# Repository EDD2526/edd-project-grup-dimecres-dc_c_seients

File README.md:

View this project on [CADLAB.io](https://cadlab.io/project/30193). 

# Projecte Seients

>**Autors: MIGUEL Angel Tovar Jaime - Pol Salas Costa** 
>**Versió: 3.8**

----------

## Objectiu

>Dissenyar una Unitat de Control Electrònic (ECU) per al control dels seients, capaç de gestionar la posició, memòria de la posició i l'escalfador del seient, comunicant-se amb la resta del vehicle mitjançant bus CAN.

## Diagrama de blocs

### Descripció/funcionalitat de cada bloc

  * **Processament Lògic:** Microcontrolador PIC24HJ128GP502 a 3.3V encarregat de l'execució del firmware i gestió de perifèrics
  * **Alimentació:** Sistema de doble regulació. Un convertidor LM2596 que redueix els 12V de la bateria a 5V per a comunicacions, i un regulador LM1117 que  proporciona 3.3V nets per a la lògica digital
  * **Control de Potència:** Controlador PWM actuant a través del bus I2C, PCA9685, per accionar els drivers dels 3 motors (posició, altura, reclinació). S'inclou un MOSFET per al control de la manta calefactora
  * **Emmagatzematge:** Memòria EEPROM I2C, 24LC256, per desar de forma no volàtil certes posicions dels seients
  * **Interfícies de Comunicació:** Transceptor MCP2562-E-SN per a connexió al bus CAN del vehicle, i MAX3232 per adaptar els nivells lògics UART a RS232 per a depuració mitjançant connector DE-9
  * **Entrades/Sensors:** Connectors per a la botonera d'usuari i finals de cursa

-----------

## Requisits / Especificacions

  * Alimentació d'entrada: 12V DC
  * Tensions de regulació interna: 5V DC i 3.3V DC
  * Microcontrolador: PIC24HJ128GP502
  * Freqüència de rellotge: Cristall extern de 8 MHz
  * Entrades digitals: 6 botons de control de seient i 3 finals de cursa agrupats
  * Comunicacions: Bus CAN, bus I2C, i port sèrie UART/RS232

-----------

## Components

| Descripció | Ref | Package | Datasheet | Proveïdor | Preu | Unitats |
| --- | --- | --- | --- | --- | --- | --- |
| Microcontrolador | PIC24HJ128GP502 | SOIC-28 | [Datasheet](https://www.microchip.com/en-us/product/PIC24HJ128GP502) | Mouser | 4,50&euro; | 1x |
| Controlador PWM I2C | PCA9685BS | HVQFN-28 | [Datasheet](https://www.nxp.com/docs/en/data-sheet/PCA9685.pdf) | Mouser | 2,10&euro; | 1x |
| Driver de Motor (Pont H) | DRV8871 | HSOP-8 | [Datasheet](https://www.ti.com/lit/ds/symlink/drv8871.pdf) | Mouser | 1,50&euro; | 3x |
| MOSFET de potència | IRLZ44N | TO-220 | [Datasheet](https://www.infineon.com/dgdl/irlz44n.pdf?fileId=5546d462533600a40153567206892720) | Mouser | 0,90&euro; | 1x |
| Memòria EEPROM I2C | 24LC256 | SOIC-8 | [Datasheet](https://ww1.microchip.com/downloads/en/DeviceDoc/21203M.pdf) | Mouser | 0,60&euro; | 1x |
| Transceptor CAN | MCP2562-E-SN | SOIC-8 | [Datasheet](https://ww1.microchip.com/downloads/en/DeviceDoc/20005167C.pdf) | Mouser | 1,10&euro; | 1x |
| Transceptor RS232 | MAX3232 | SOIC-16 | [Datasheet](https://www.ti.com/lit/ds/symlink/max3232.pdf) | Mouser | 1,20&euro; | 1x |
| Expansor I/O I2C | PCF8574T | SOIC-16 | [Datasheet](https://www.ti.com/lit/ds/symlink/pcf8574.pdf) | Mouser | 1,30&euro; | 1x |
| Regulador (12V a 5V) | LM2596 | TO-263 | [Datasheet](https://www.ti.com/lit/ds/symlink/lm2596.pdf) | Mouser | 1,50&euro; | 1x |
| Regulador (5V a 3.3V) | LM1117 | TO-252 | [Datasheet](https://www.ti.com/lit/ds/symlink/lm1117.pdf) | Mouser | 0,80&euro; | 1x |
| Connector RS232 | DE-9_socket (Femella)| THT | - | Mouser | 1,00&euro; | 1x |
| Connector CAN | DE-9_plug (Mascle) | THT | - | Mouser | 1,00&euro; | 1x |
| Sensor cinturó | 5F0857756YLZ | OEM | - | Recanvis VAG | 45,00&euro; | 1x |
| Motor DC amb reductora | JGY370 (12V, 30 RPM) | Eix 6mm D | - | Genèric | 9,00&euro; | 3x |
| Manta Calefactora | Carbon Fiber Pad | Genèric | - | Genèric | 15,00&euro; | 1x |
| Sensor Temperatura | Termistor NTC 10k | Gota / Cable| [Datasheet](https://www.vishay.com/docs/29049/ntcle100.pdf) | Genèric | 0,50€ | 1x |
| Sensor de Temperatura | TMP102 | DRL SOT563 | [Datasheet](https://www.ti.com/lit/ds/symlink/tmp102.pdf) | Texas Instruments | 0,323€ | 1x |

-----------

## Software

### Eines:

  * KiCad 9.0 o superior
  * 

### Configuraci&#243; :

  * 

### Funcionalitats:

  * 

-----------

## Historial de canvis

| Data | Autor     | Branch | Versi&#243; | Descripci&#243; |
| --- | --- | --- | --- | --- |
|  28/03/2023 | mlopez | Master | initial commit | Primera versi&#243; d'esquem&#224;tic i selecci&#243; de components |
| 17/03/2026 | Pol i Miguel | main | 1.0 | Finalització de l'esquemàtic |
| 20/04/2026 | Pol i Miguel | main | 3.9 | Finalització del layout |

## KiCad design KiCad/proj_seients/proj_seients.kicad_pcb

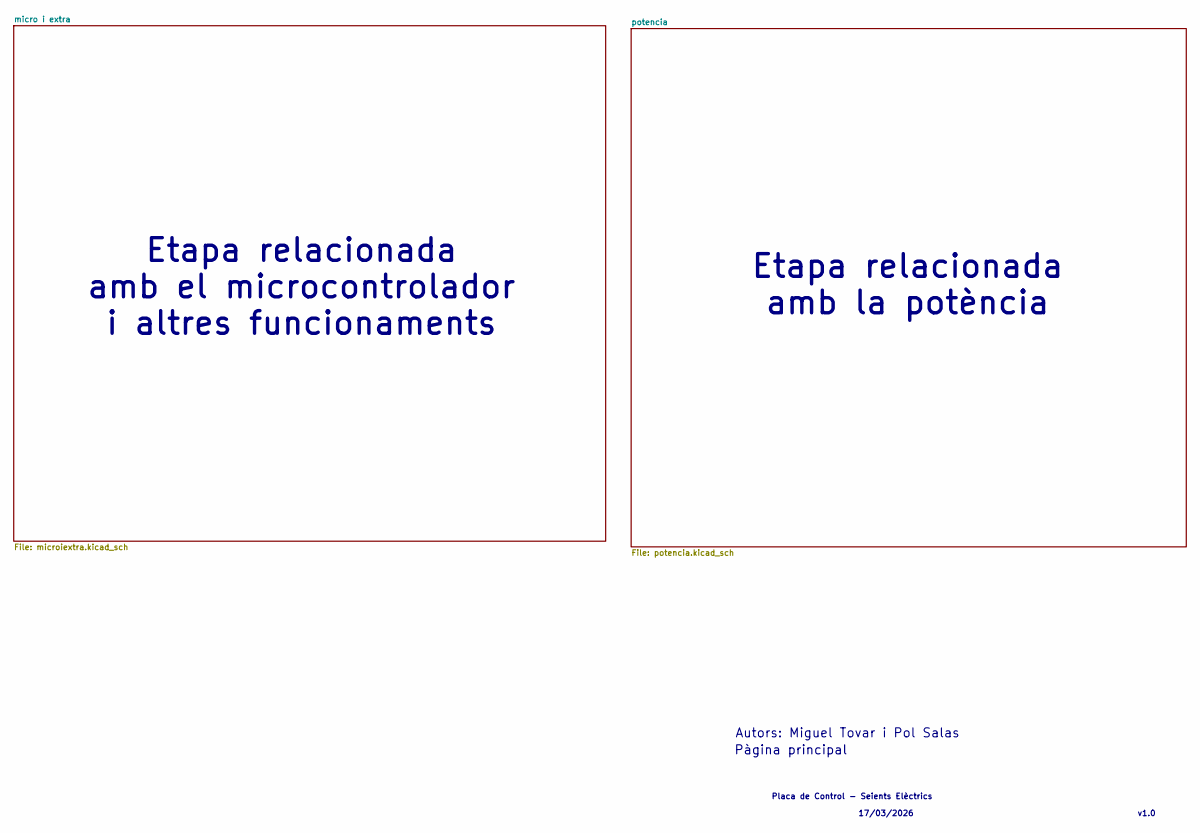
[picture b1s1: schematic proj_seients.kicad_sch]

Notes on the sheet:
v1.0
Etapa relacionada amb el microcontrolador i altres funcionaments
Placa de Control - Seients Elèctrics
Etapa relacionada amb la potència
17/03/2026
Pàgina principal
Autors: Miguel Tovar i Pol Salas

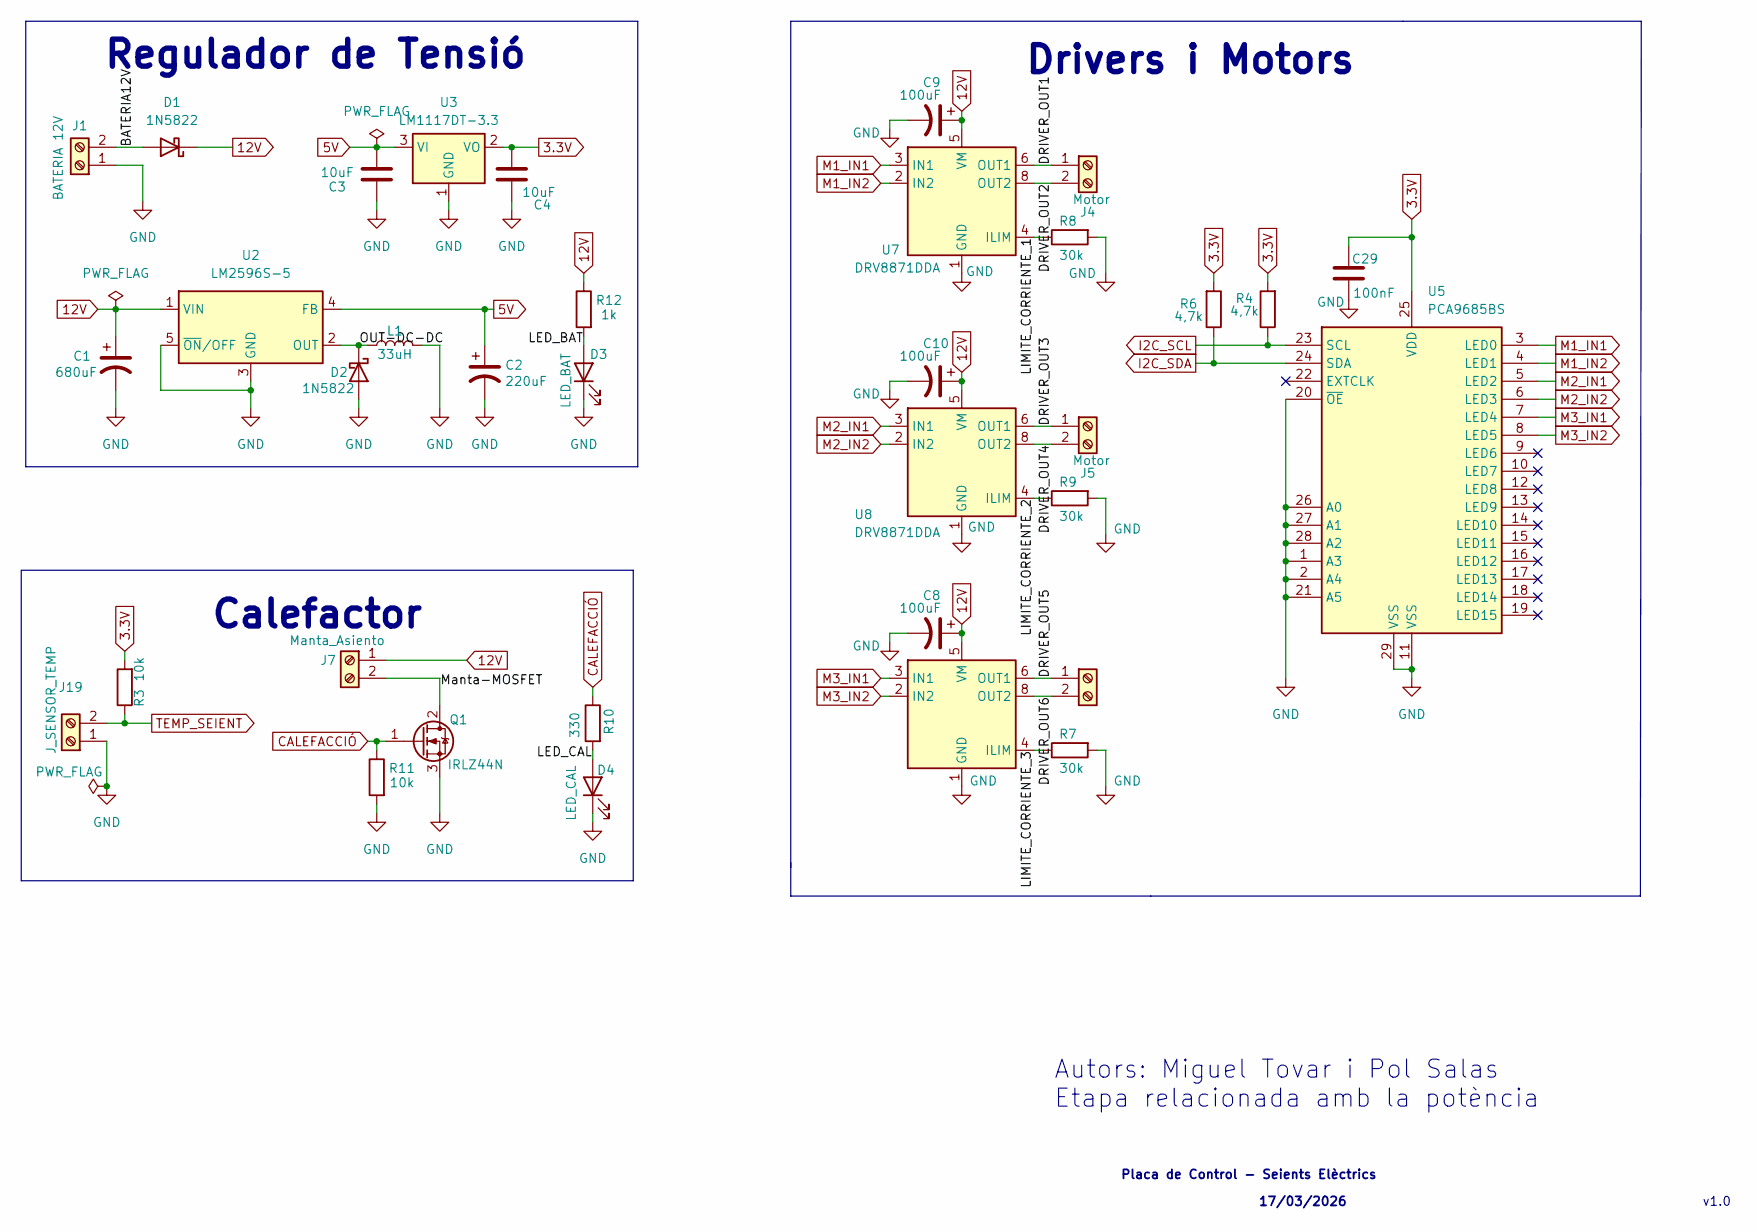
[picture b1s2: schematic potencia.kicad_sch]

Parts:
C1: 680uF; CP_Radial_D10.0mm_P5.00mm
C2: 220uF; CP_Radial_D8.0mm_P3.50mm
C3, C4: 10uF; C_0805_2012Metric
C8, C9, C10: 100uF; CP_Radial_D8.0mm_P3.50mm
C29: 100nF; C_0805_2012Metric
D1, D2: 1N5822; D_DO-201AD_P15.24mm_Horizontal
D3: LED_BAT; LED_0805_2012Metric
D4: LED_CAL; LED_0805_2012Metric
J1: BATERIA 12V; TerminalBlock_Phoenix_MKDS-1,5-2-5.08_1x02_P5.08mm_Horizont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
J4, J5, J6: Motor; TerminalBlock_Phoenix_MKDS-1,5-2-5.08_1x02_P5.08mm_Horizont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
J7: Manta_Asiento; TerminalBlock_Phoenix_MKDS-1,5-2-5.08_1x02_P5.08mm_Horizont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
J19: J_SENSOR_TEMP; TerminalBlock_Phoenix_MKDS-1,5-2-5.08_1x02_P5.08mm_Horizont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
L1: 33uH; L_Radial_D10.0mm_P5.00mm_Fastron_07M
Q1: IRLZ44N; TO-220-3_Vertical
R3, R11: 10k; R_0805_2012Metric
R4, R6: 4,7k; R_0805_2012Metric
R7, R8, R9: 30k; R_0805_2012Metric
R10: 330; R_0805_2012Metric
R12: 1k; R_0805_2012Metric
U2: LM2596S-5; TO-263-5_TabPin3
U3: LM1117DT-3.3; TO-252-3_TabPin2
U5: PCA9685BS; QFN-28-1EP_6x6mm_P0.65mm_EP4.25x4.25mm
U6, U7, U8: DRV8871DDA; Texas_HTSOP-8-1EP_3.9x4.9mm_P1.27mm_EP2.95x4.9mm_Mask2.4x3.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

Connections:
3.3V: C4.2, C29.2, R3.2, R4.2, R6.2, U3.2 (VO), U5.25 (VDD); also elsewhere on the board
5V: C2.1, C3.2, U2.4 (FB), U3.3 (VI); also elsewhere on the board
12V: C1.1, C8.1, C9.1, C10.1, D1.1 (K), J7.1, R12.1, U2.1 (VIN), U6.5 (VM), U7.5 (VM), U8.5 (VM); also elsewhere on the board
/potencia/BATERIA12V: D1.2 (A), J1.2
/potencia/DRIVER_OUT1: J4.1, U7.6 (OUT1)
/potencia/DRIVER_OUT2: J4.2, U7.8 (OUT2)
/potencia/DRIVER_OUT3: J5.1, U8.6 (OUT1)
/potencia/DRIVER_OUT4: J5.2, U8.8 (OUT2)
/potencia/DRIVER_OUT5: J6.1, U6.6 (OUT1)
/potencia/DRIVER_OUT6: J6.2, U6.8 (OUT2)
/potencia/LED_BAT: D3.2 (A), R12.2
/potencia/LED_CAL: D4.2 (A), R10.2
/potencia/LIMITE_CORRIENTE_1: R8.1, U7.4 (ILIM)
/potencia/LIMITE_CORRIENTE_2: R9.1, U8.4 (ILIM)
/potencia/LIMITE_CORRIENTE_3: R7.1, U6.4 (ILIM)
/potencia/Manta-MOSFET: J7.2, Q1.2 (D)
/potencia/OUT-DC-DC: D2.1 (K), L1.1, U2.2 (OUT)
CALEFACCIÓ: Q1.1 (G), R10.1, R11.1; also elsewhere on the board
GND: C1.2, C2.2, C3.1, C4.1, C8.2, C9.2, C10.2, C29.1, D2.2 (A), D3.1 (K), D4.1 (K), J1.1, J19.1, L1.2, Q1.3 (S), R7.2, R8.2, R9.2, R11.2, U2.3 (GND), U2.5 (~ON/OFF), U3.1 (GND), U5.1 (A3), U5.2 (A4), U5.11 (VSS), U5.20 (~OE), U5.21 (A5), U5.26 (A0), U5.27 (A1), U5.28 (A2), U5.29 (VSS), U6.1 (GND), U6.7 (GND), U6.9 (GND), U7.1 (GND), U7.7 (GND), U7.9 (GND), U8.1 (GND), U8.7 (GND), U8.9 (GND); also elsewhere on the board
I2C_SCL: R4.1, U5.23 (SCL); also elsewhere on the board
I2C_SDA: R6.1, U5.24 (SDA); also elsewhere on the board
M1_IN1: U5.3 (LED0), U7.3 (IN1)
M1_IN2: U5.4 (LED1), U7.2 (IN2)
M2_IN1: U5.5 (LED2), U8.3 (IN1)
M2_IN2: U5.6 (LED3), U8.2 (IN2)
M3_IN1: U5.7 (LED4), U6.3 (IN1)
M3_IN2: U5.8 (LED5), U6.2 (IN2)
TEMP_SEIENT: J19.2, R3.1; also elsewhere on the board

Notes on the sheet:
Regulador de Tensió
Placa de Control - Seients Elèctrics
17/03/2026
Drivers i Motors
Calefactor
Autors: Miguel Tovar i Pol Salas Etapa relacionada amb la potència
v1.0

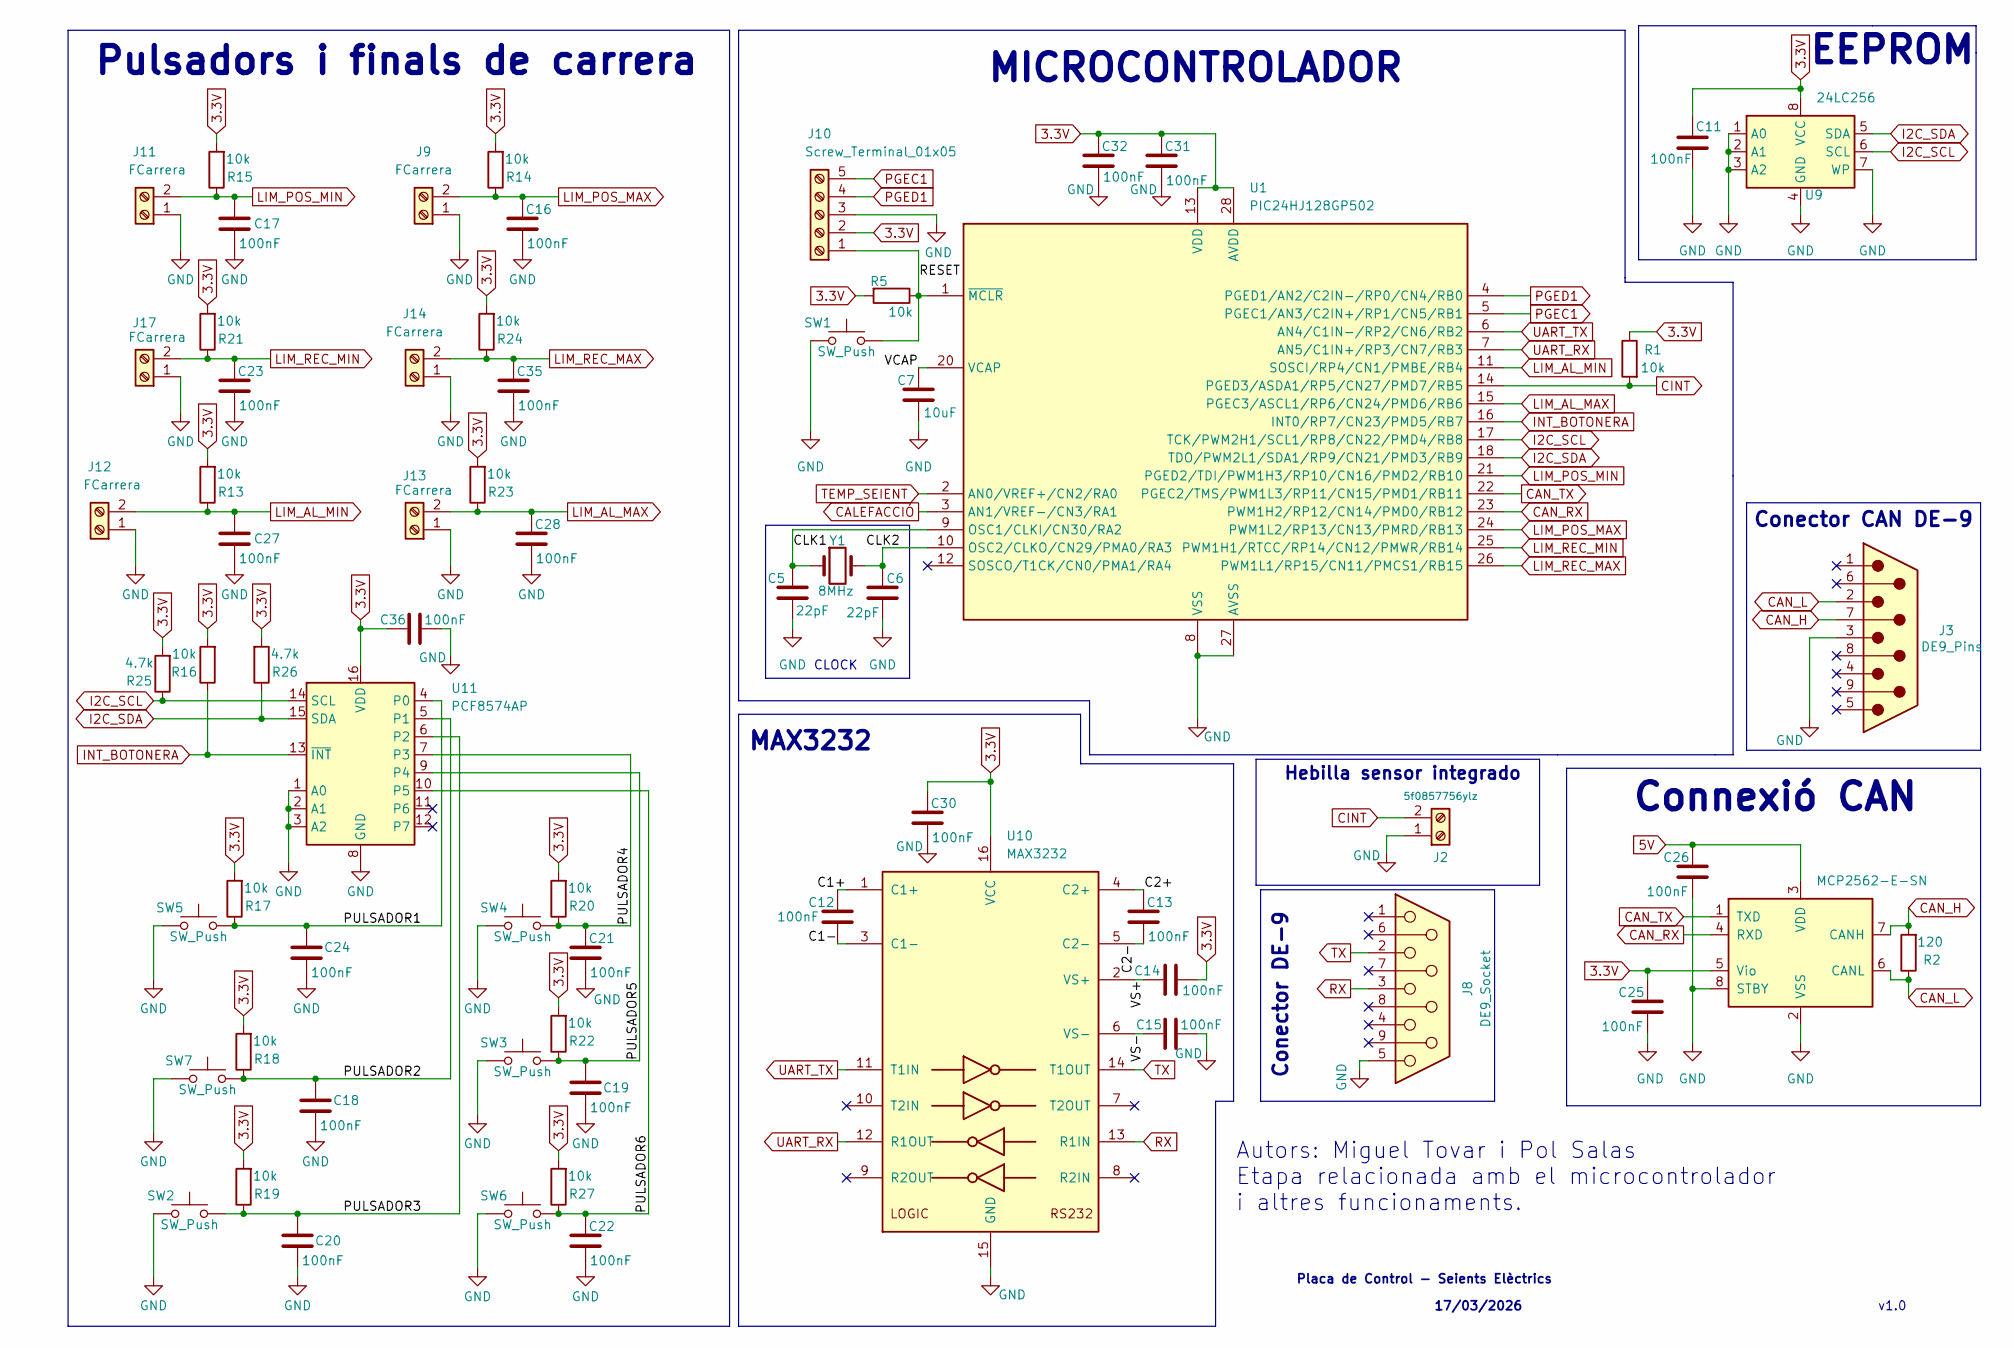
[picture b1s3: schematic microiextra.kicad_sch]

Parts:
C5, C6: 22pF; C_0805_2012Metric
C7: 10uF; C_0805_2012Metric
C11, C12, C13, C14, C15, C16, C17, C18, C19, C20, C21, C22, C23, C24, C25, C26, C27, C28, C30, C31, C32, C35, C36: 100nF; C_0805_2012Metric
J2: 5f0857756ylz; TerminalBlock_Phoenix_MKDS-1,5-2-5.08_1x02_P5.08mm_Horizont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
J3: DE9_Pins; DSUB-9_Pins_Horizontal_P2.77x2.84mm_EdgePinOffset9.40mm
J8: DE9_Socket; DSUB-9_Socket_Horizontal_P2.77x2.84mm_EdgePinOffset9.40mm
J9, J11, J12, J13, J14, J17: FCarrera; PinHeader_1x02_P2.54mm_Vertical
J10: Screw_Terminal_01x05; PinHeader_1x05_P2.54mm_Vertical
R1, R5, R13, R14, R15, R16, R17, R18, R19, R20, R21, R22, R23, R24, R27: 10k; R_0805_2012Metric
R2: 120; R_0805_2012Metric
R25, R26: 4.7k; R_0805_2012Metric
SW1, SW2, SW3, SW4, SW5, SW6, SW7: SW_Push; SW_PUSH_6mm
U1: PIC24HJ128GP502; SOIC-28W_7.5x17.9mm_P1.27mm
U4: MCP2562-E-SN; SOIC-8_3.9x4.9mm_P1.27mm
U9: 24LC256; SOIC-8_3.9x4.9mm_P1.27mm
U10: MAX3232; SOIC-16_3.9x9.9mm_P1.27mm
U11: PCF8574AP; DIP-16_W7.62mm
Y1: 8MHz; Crystal_HC49-U_Vertical

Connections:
3.3V: C11.1, C14.1, C25.2, C30.2, C31.2, C32.2, C36.2, J10.2, R1.1, R5.2, R13.2, R14.2, R15.2, R16.2, R17.2, R18.2, R19.2, R20.2, R21.2, R22.2, R23.2, R24.2, R25.2, R26.2, R27.2, U1.13 (VDD), U1.28 (AVDD), U4.5 (Vio), U9.8 (VCC), U10.16 (VCC), U11.16 (VDD); also elsewhere on the board
5V: C26.2, U4.3 (VDD); also elsewhere on the board
/micro i extra/C1+: C12.2, U10.1 (C1+)
/micro i extra/C1-: C12.1, U10.3 (C1-)
/micro i extra/C2+: C13.2, U10.4 (C2+)
/micro i extra/C2-: C13.1, U10.5 (C2-)
/micro i extra/CLK1: C5.2, U1.9 (OSC1/CLKI/CN30/RA2), Y1.1
/micro i extra/CLK2: C6.2, U1.10 (OSC2/CLKO/CN29/PMA0/RA3), Y1.2
/micro i extra/PULSADOR1: C24.2, R17.1, SW5.2, U11.4 (P0)
/micro i extra/PULSADOR2: C18.2, R18.1, SW7.2, U11.5 (P1)
/micro i extra/PULSADOR3: C20.2, R19.1, SW2.2, U11.6 (P2)
/micro i extra/PULSADOR4: C21.2, R20.1, SW4.2, U11.7 (P3)
/micro i extra/PULSADOR5: C19.2, R22.1, SW3.2, U11.9 (P4)
/micro i extra/PULSADOR6: C22.2, R27.1, SW6.2, U11.10 (P5)
/micro i extra/RESET: J10.1, R5.1, SW1.2, U1.1 (~MCLR)
/micro i extra/VCAP: C7.2, U1.20 (VCAP)
/micro i extra/VS+: C14.2, U10.2 (VS+)
/micro i extra/VS-: C15.2, U10.6 (VS-)
CALEFACCIÓ: U1.3 (AN1/VREF-/CN3/RA1); also elsewhere on the board
CAN_H: J3.7, R2.2, U4.7 (CANH)
CAN_L: J3.2, R2.1, U4.6 (CANL)
CAN_RX: U1.23 (PWM1H2/RP12/CN14/PMD0/RB12), U4.4 (RXD)
CAN_TX: U1.22 (PGEC2/TMS/PWM1L3/RP11/CN15/PMD1/RB11), U4.1 (TXD)
CINT: J2.2, R1.2, U1.14 (PGED3/ASDA1/RP5/CN27/PMD7/RB5)
GND: C5.1, C6.1, C7.1, C11.2, C15.1, C16.1, C17.1, C18.1, C19.1, C20.1, C21.1, C22.1, C23.1, C24.1, C25.1, C26.1, C27.1, C28.1, C30.1, C31.1, C32.1, C35.1, C36.1, J2.1, J3.3, J8.5, J9.1, J10.3, J11.1, J12.1, J13.1, J14.1, J17.1, SW1.1, SW2.1, SW3.1, SW4.1, SW5.1, SW6.1, SW7.1, U1.8 (VSS), U1.19 (VSS), U1.27 (AVSS), U4.2 (VSS), U4.8 (STBY), U9.1 (A0), U9.2 (A1), U9.3 (A2), U9.4 (GND), U9.7 (WP), U10.15 (GND), U11.1 (A0), U11.2 (A1), U11.3 (A2), U11.8 (GND); also elsewhere on the board
I2C_SCL: R25.1, U1.17 (TCK/PWM2H1/SCL1/RP8/CN22/PMD4/RB8), U9.6 (SCL), U11.14 (SCL); also elsewhere on the board
I2C_SDA: R26.1, U1.18 (TDO/PWM2L1/SDA1/RP9/CN21/PMD3/RB9), U9.5 (SDA), U11.15 (SDA); also elsewhere on the board
INT_BOTONERA: R16.1, U1.16 (INT0/RP7/CN23/PMD5/RB7), U11.13 (~INT)
LIM_AL_MAX: C28.2, J13.2, R23.1, U1.15 (PGEC3/ASCL1/RP6/CN24/PMD6/RB6)
LIM_AL_MIN: C27.2, J12.2, R13.1, U1.11 (SOSCI/RP4/CN1/PMBE/RB4)
LIM_POS_MAX: C16.2, J9.2, R14.1, U1.24 (PWM1L2/RP13/CN13/PMRD/RB13)
LIM_POS_MIN: C17.2, J11.2, R15.1, U1.21 (PGED2/TDI/PWM1H3/RP10/CN16/PMD2/RB10)
LIM_REC_MAX: C35.2, J14.2, R24.1, U1.26 (PWM1L1/RP15/CN11/PMCS1/RB15)
LIM_REC_MIN: C23.2, J17.2, R21.1, U1.25 (PWM1H1/RTCC/RP14/CN12/PMWR/RB14)
PGEC1: J10.5, U1.5 (PGEC1/AN3/C2IN+/RP1/CN5/RB1)
PGED1: J10.4, U1.4 (PGED1/AN2/C2IN-/RP0/CN4/RB0)
RX: J8.3, U10.13 (R1IN)
TEMP_SEIENT: U1.2 (AN0/VREF+/CN2/RA0); also elsewhere on the board
TX: J8.2, U10.14 (T1OUT)
UART_RX: U1.7 (AN5/C1IN+/RP3/CN7/RB3), U10.12 (R1OUT)
UART_TX: U1.6 (AN4/C1IN-/RP2/CN6/RB2), U10.11 (T1IN)

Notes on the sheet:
Hebilla sensor integrado
Conector DE-9
MICROCONTROLADOR
v1.0
17/03/2026
CLOCK
Placa de Control - Seients Elèctrics
Autors: Miguel Tovar i Pol Salas Etapa relacionada amb el microcontrolador i altres funcionaments.
EEPROM
MAX3232
Conector CAN DE-9
Pulsadors i finals de carrera
Connexió CAN

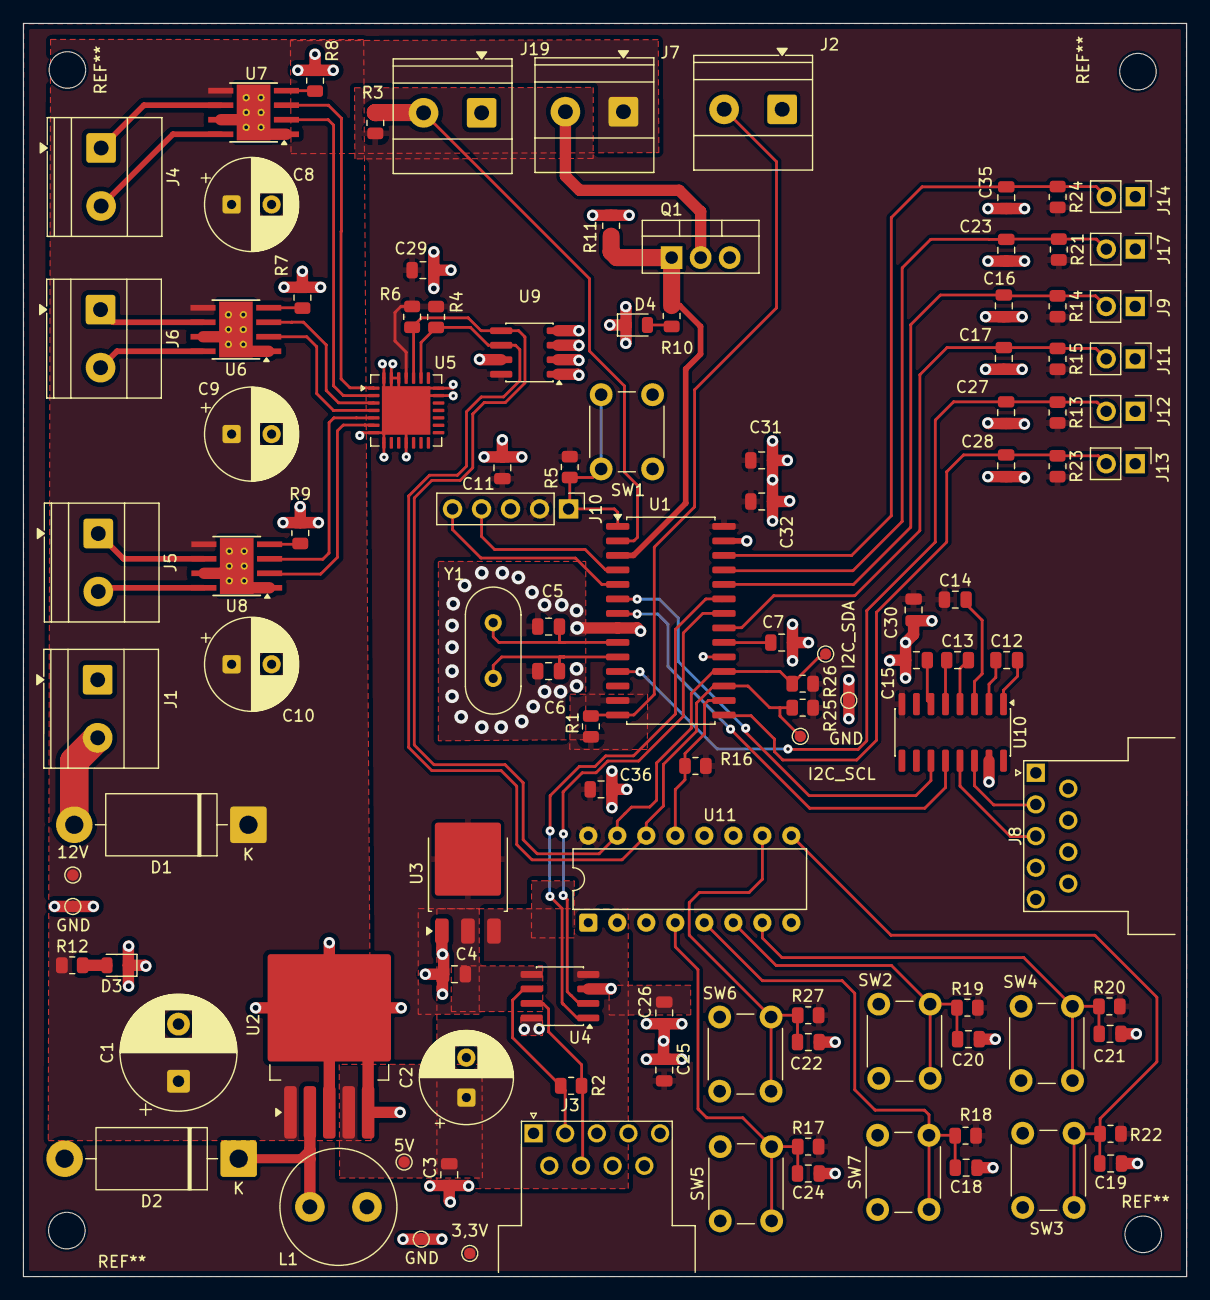
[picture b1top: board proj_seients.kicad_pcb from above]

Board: 2 copper layers, 101.8 x 109.7 mm, 110 parts (0 on the bottom side), 62 nets.

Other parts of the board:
3,3V, 5V, 12V: TestPoint_Pad_D1.0mm
GND: TestPoint_Pad_D1.0mm
GND#2, GND#3: TestPoint_Pad_D1.0mm
I2C_SCL, I2C_SDA: TestPoint_Pad_D1.0mm

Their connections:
3.3V: 3,3V.1; also elsewhere on the board
5V: 5V.1; also elsewhere on the board
12V: 12V.1; also elsewhere on the board
GND: GND.1, GND#2.1, GND#3.1; also elsewhere on the board
I2C_SCL: I2C_SCL.1; also elsewhere on the board
I2C_SDA: I2C_SDA.1; also elsewhere on the board

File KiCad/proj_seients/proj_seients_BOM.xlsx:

Referencia | Descripción | Value | Footprint | Cantidad | Proveedor | Precio unitario (€) | Coste total (€) | Datasheet
U1 | Microcontrolador PIC24HJ128GP502 | PIC24HJ128GP502 | Package_SO:SOIC-28W_7.5x17.9mm_P1.27mm | 1 |  |  |  | http://ww1.microchip.com/downloads/en/DeviceDoc/70291G.pdf
U2 | Convertidor 12V-5V | LM2596S-5 | Package_TO_SOT_SMD:TO-263-5_TabPin3 | 1 |  |  |  | http://www.ti.com/lit/ds/symlink/lm2596.pdf
U3 | Regulador 3.3V | LM1117DT-3.3 | Package_TO_SOT_SMD:TO-252-3_TabPin2 | 1 |  |  |  | http://www.ti.com/lit/ds/symlink/lm1117.pdf
U4 | Transceptor CAN | MCP2562-E-SN | Package_SO:SOIC-8_3.9x4.9mm_P1.27mm | 1 |  |  |  | http://ww1.microchip.com/downloads/en/DeviceDoc/25167A.pdf
U5 | Driver PWM | PCA9685BS | Package_DFN_QFN:QFN-28-1EP_6x6mm_P0.65mm_EP4.25x4.25mm | 1 |  |  |  | http://www.nxp.com/docs/en/data-sheet/PCA9685.pdf
U6,U7,U8 | Driver Motor | DRV8871DDA | Package_SO:Texas_HTSOP-8-1EP_3.9x4.9mm_P1.27mm_EP2.95x4.9mm_Mask2.4x3.1mm_Therm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 | 3 |  |  |  | http://www.ti.com/lit/ds/symlink/drv8871.pdf
U9 | EEPROM | 24LC256 | Package_SO:SOIC-8_3.9x4.9mm_P1.27mm | 1 |  |  |  | http://ww1.microchip.com/downloads/en/devicedoc/21203m.pdf
U10 | RS232 Transceiver | MAX3232 | Package_SO:SOIC-16_3.9x9.9mm_P1.27mm | 1 |  |  |  | https://datasheets.maximintegrated.com/en/ds/MAX3222-MAX3241.pdf
U11 | Expansor IO | PCF8574AP | Package_DIP:DIP-16_W7.62mm | 1 |  |  |  | https://www.nxp.com/docs/en/data-sheet/PCF8574_PCF8574A.pdf
Y1 | Cristal 8MHz | 8MHz | Crystal:Crystal_HC49-U_Vertical | 1 |  |  |  | ~
C1 | Condensador electrolítico 680uF 25V | 680uF | Capacitor_THT:CP_Radial_D10.0mm_P5.00mm | 1 |  |  |  | ~
C2 | Condensador electrolítico 220uF 25V | 220uF | Capacitor_THT:CP_Radial_D8.0mm_P3.50mm | 1 |  |  |  | ~
C3,C4,C7 | Condensador cerámico 10uF 0805 | 10uF | Capacitor_SMD:C_0805_2012Metric | 3 |  |  |  | ~
C5,C6 | Condensador cerámico 22pF 0805 | 22pF | Capacitor_SMD:C_0805_2012Metric | 2 |  |  |  | ~
C8,C9,C10 | Condensador electrolítico 100uF | 100uF | Capacitor_THT:CP_Radial_D8.0mm_P3.50mm | 3 |  |  |  | ~
C11-C32,C35,C36 | Condensador cerámico 100nF 0805 | 100nF | Capacitor_SMD:C_0805_2012Metric | 24 |  |  |  | ~
R1,R3,R5,R11,R13-R24,R27 | Resistencias 10kΩ | 10k | Resistor_SMD:R_0805_2012Metric | 17 |  |  |  | ~
R2 | Resistencia 120Ω | 120 | Resistor_SMD:R_0805_2012Metric | 1 |  |  |  | ~
R4,R6,R25,R26 | Resistencias 4.7kΩ | 4.7k | Resistor_SMD:R_0805_2012Metric | 4 |  |  |  | ~
R7,R8,R9 | Resistencias 30kΩ | 30k | Resistor_SMD:R_0805_2012Metric | 3 |  |  |  | ~
R10 | Resistencia 330Ω | 330 | Resistor_SMD:R_0805_2012Metric | 1 |  |  |  | ~
R12 | Resistencia 1kΩ | 1k | Resistor_SMD:R_0805_2012Metric | 1 |  |  |  | ~
D1,D2 | Diodo Schottky 1N5822 | 1N5822 | Diode_THT:D_DO-201AD_P15.24mm_Horizontal | 2 |  |  |  | http://www.vishay.com/docs/88526/1n5820.pdf
D3 | LED Indicador batería | LED_BAT | LED_SMD:LED_0805_2012Metric | 1 |  |  |  | ~
D4 | LED Indicador calefacción | LED_CAL | LED_SMD:LED_0805_2012Metric | 1 |  |  |  | ~
L1 | Inductor 33uH | 33uH | Inductor_THT:L_Radial_D10.0mm_P5.00mm_Fastron_07M | 1 |  |  |  | ~
Q1 | MOSFET IRLZ44N | IRLZ44N | Package_TO_SOT_THT:TO-220-3_Vertical | 1 |  |  |  | http://www.irf.com/product-info/datasheets/data/irlz44n.pdf
SW1-SW7 | Pulsadores | SW_Push | Button_Switch_THT:SW_PUSH_6mm | 7 |  |  |  | ~
J1 | Entrada alimentación 12V | BATERIA 12V | TerminalBlock_Phoenix:TerminalBlock_Phoenix_MKDS-1,5-2-5.08_1x02_P5.08mm_Horizo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 | 1 |  |  |  | ~
J2 | Conector genérico | 5f0857756ylz | TerminalBlock_Phoenix:TerminalBlock_Phoenix_MKDS-1,5-2-5.08_1x02_P5.08mm_Horizo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 | 1 |  |  |  | ~
J3 | Conector DB9 Macho | DE9_Pins | Connector_Dsub:DSUB-9_Pins_Horizontal_P2.77x2.84mm_EdgePinOffset9.40mm | 1 |  |  |  | ~
J4,J5,J6 | Salida motor | Motor | TerminalBlock_Phoenix:TerminalBlock_Phoenix_MKDS-1,5-2-5.08_1x02_P5.08mm_Horizo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 | 3 |  |  |  | ~
J7 | Manta calefactora | Manta_Asiento | TerminalBlock_Phoenix:TerminalBlock_Phoenix_MKDS-1,5-2-5.08_1x02_P5.08mm_Horizo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 | 1 |  |  |  | ~
J8 | Conector DB9 Hembra | DE9_Socket | Connector_Dsub:DSUB-9_Socket_Horizontal_P2.77x2.84mm_EdgePinOffset9.40mm | 1 |  |  |  | ~
J9,J11,J12,J13,J14,J17 | Final de carrera | FCarrera | Connector_PinHeader_2.54mm:PinHeader_1x02_P2.54mm_Vertical | 6 |  |  |  | ~
J10 | Terminal 5 pines | Screw_Terminal_01x05 | Connector_PinHeader_2.54mm:PinHeader_1x05_P2.54mm_Vertical | 1 |  |  |  | ~
J19 | Sensor temperatura | J_SENSOR_TEMP | TerminalBlock_Phoenix:TerminalBlock_Phoenix_MKDS-1,5-2-5.08_1x02_P5.08mm_Horizo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 | 1 |  |  |  | ~

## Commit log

2026-03-11 Projecte KiCad
2026-03-11 Update project name and author details in README
2026-03-16 Afegit Regulador de Tensió
2026-03-16 Afegit Regulador de tensió + Sensor Cinturó + CAN
2026-03-16 Backlink to CADLAB.io has been added.
2026-03-17 Afegit drivers + motors
2026-03-17 Modificació de recuadres
2026-03-17 Afegit calefacor + alguns LEDs
2026-03-17 Afegit EEPROM
2026-03-17 Afegit MAX3232
2026-03-17 Tot Afegit
2026-03-17 Canvi Connexió AVDD i AVSS
2026-03-17 Correcions proposades
2026-03-17 Canvis visuals
2026-03-17 Revise version and project objective in README
    Updated version number and clarified project objective.
2026-03-17 Fix image syntax for block diagram in README
2026-03-17 Fix block diagram image path in README
    Updated the image path for the block diagram in README.
2026-03-17 Fix image path for block diagram in README
2026-03-17 Revise hardware descriptions and specifications in README
    Updated the description of components and requirements in the README.
2026-03-17 Simplify data table in README
    Removed redundant columns from the data table.
2026-03-17 Fix duplicate section header in README
    Removed duplicate 'Components' section header.
2026-03-18 eliminat arxiu unnamed que era incorrecte
2026-03-18 canvi r pull driver
2026-03-20 Canvi de TCAN i Afegit CAN DE.9
2026-03-20 Afegit C protecció als 5V del CAN
2026-03-21 Canvis de pulsadors, estètica dels drivers i commentaris extres
2026-03-21 Canvi taula de components al readme
2026-03-21 Huellas agefides
2026-03-22 Començament layout
2026-03-22 Versió 1.0 Layout
2026-03-22 Versió 1.1 Layout
2026-03-22 Versió 2.0 Layout
2026-03-22 Versió 2.1 Layout
2026-03-23 Versió 2.2 Layout
2026-03-23 Afegit títol i autors a la placa
2026-03-24 Version V2.4
2026-03-24 Exclusió de dos errors justificats
2026-03-24 V2.5
2026-03-24 Versió 3.0
2026-03-24 Actualización del diagrama de bloques
2026-03-25 Añadido sensor TMP102 a la lista de componentes
2026-03-25 V3.2
2026-03-31 V3.3
2026-03-31 V3.4
2026-03-31 V3.5
2026-04-07 Fix alguns errors en millora-pcb
2026-04-08 V3.6
2026-04-15 V3.7
2026-04-15 V3.8
2026-04-20 V3.9
2026-04-27 Añadido BOM sin terminar
2026-04-27 Archivo excel quitado para evitar problemas
2026-04-27 Update version to 3.8 and add layout completion entry
    Updated version numbers and added a new entry in the software table.
2026-04-28 Añadido BOM, Gerbers, CPL
